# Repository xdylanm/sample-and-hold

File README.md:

# Sample and Hold

A sample and hold circuit for a modular synth (Eurorack format) based on the LF398.

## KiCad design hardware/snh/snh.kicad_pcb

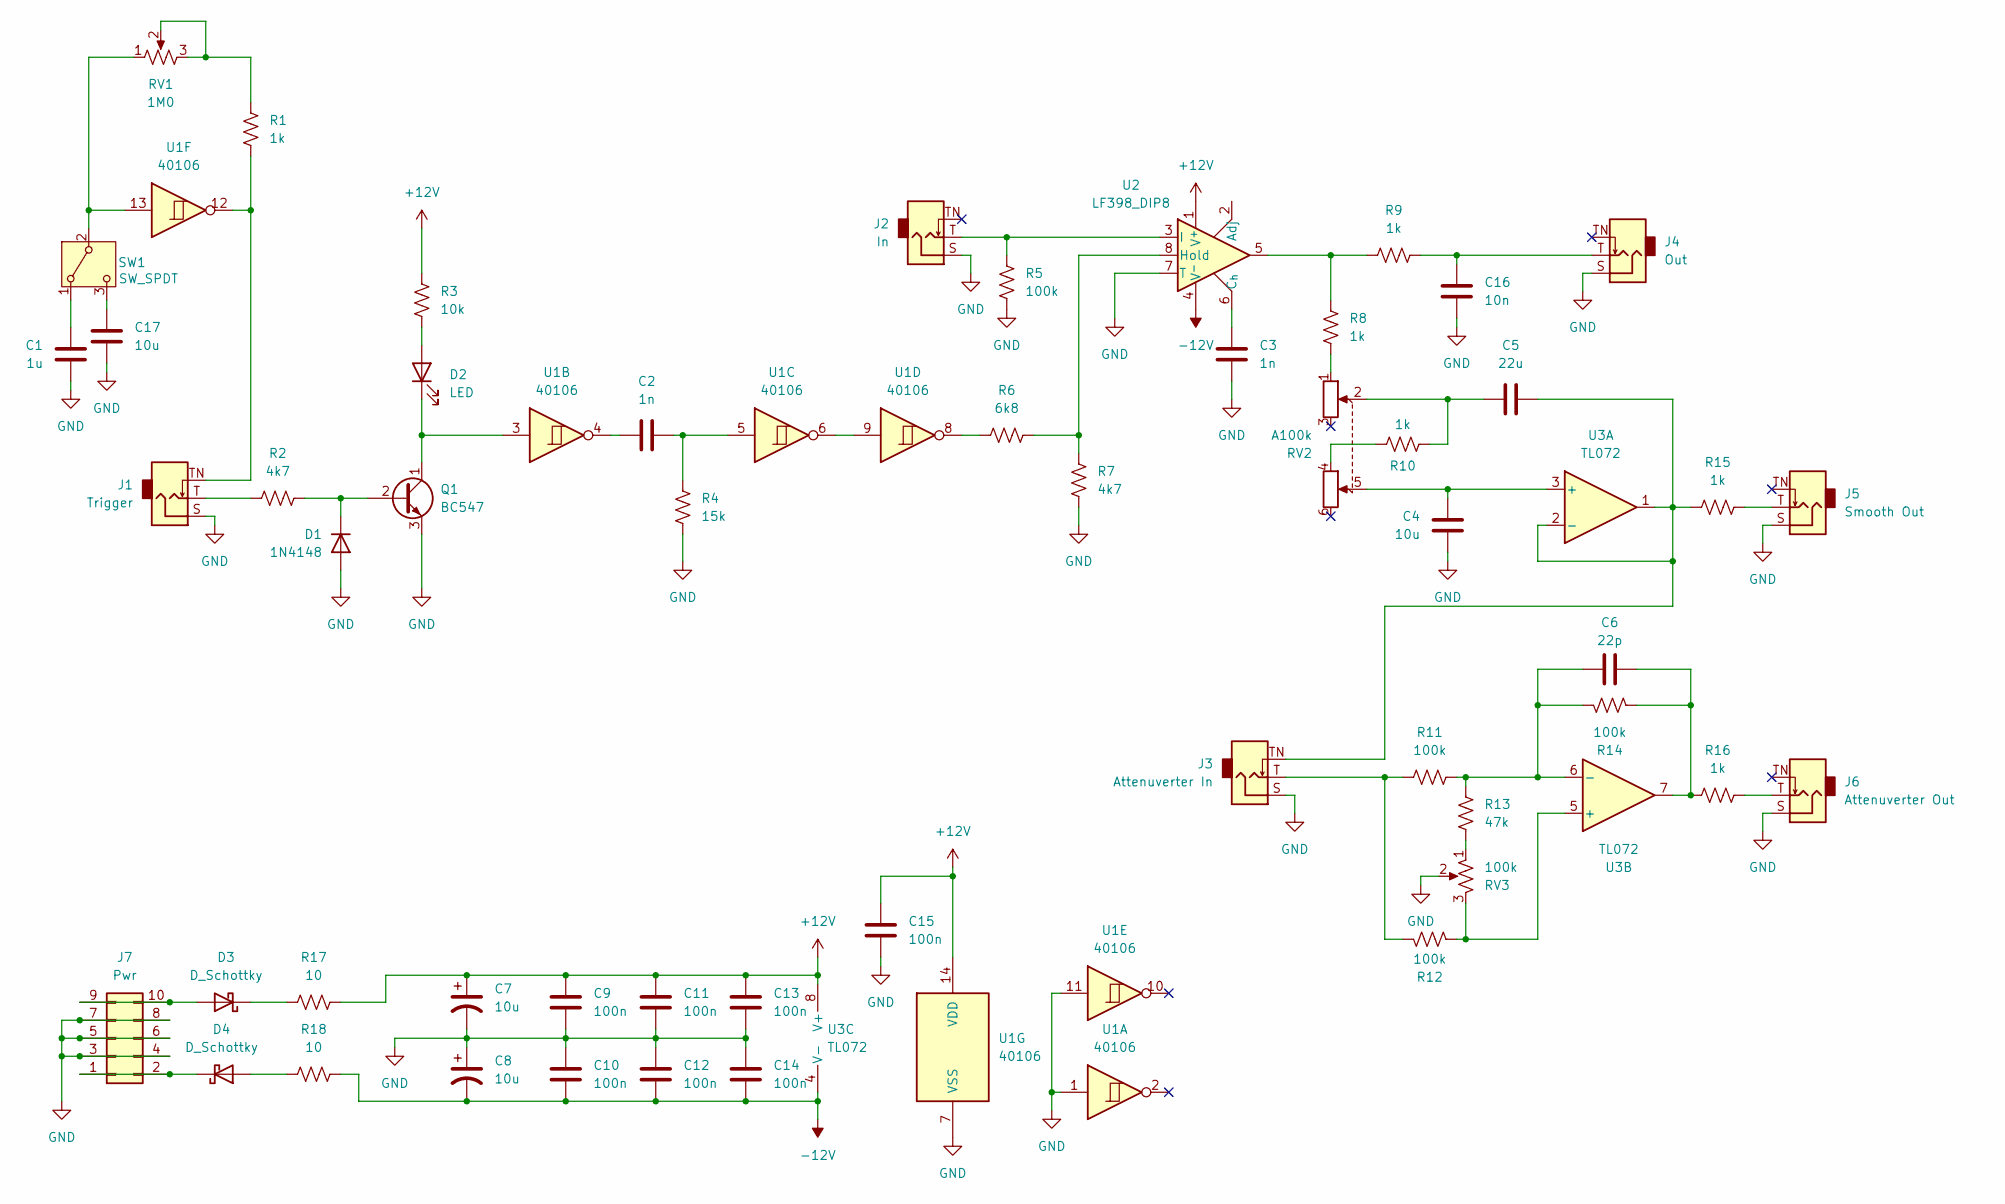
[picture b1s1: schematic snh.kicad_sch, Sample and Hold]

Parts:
C1: 1u; C_Disc_D4.7mm_W2.5mm_P5.00mm
C2: 1n; C_Disc_D5.0mm_W2.5mm_P5.00mm
C3: 1n; C_Rect_L7.0mm_W2.0mm_P5.00mm
C4, C17: 10u; C_Disc_D4.7mm_W2.5mm_P5.00mm
C5: 22u; C_Disc_D4.7mm_W2.5mm_P5.00mm
C6: 22p; C_Disc_D4.7mm_W2.5mm_P5.00mm
C7, C8: 10u; CP_Radial_D4.0mm_P2.00mm
C9, C10, C11, C12, C13, C14, C15: 100n; C_Disc_D4.7mm_W2.5mm_P5.00mm
C16: 10n; C_Disc_D4.7mm_W2.5mm_P5.00mm
D1: 1N4148; D_DO-35_SOD27_P2.54mm_Vertical_AnodeUp
D2: LED; LED_D3.0mm_Clear
D3, D4: D_Schottky; D_DO-35_SOD27_P2.54mm_Vertical_AnodeUp
J1: Trigger; Jack_3.5mm_QingPu_WQP-PJ301M-12_Vertical
J2: In; Jack_3.5mm_QingPu_WQP-PJ301M-12_Vertical
J3: Attenuverter In; Jack_3.5mm_QingPu_WQP-PJ301M-12_Vertical
J4: Out; Jack_3.5mm_QingPu_WQP-PJ301M-12_Vertical
J5: Smooth Out; Jack_3.5mm_QingPu_WQP-PJ301M-12_Vertical
J6: Attenuverter Out; Jack_3.5mm_QingPu_WQP-PJ301M-12_Vertical
J7: Pwr; IDC-Header_2x05_P2.54mm_Vertical
Q1: BC547; TO-92_Inline_Wide
R1, R8, R9, R10, R15, R16: 1k; R_Axial_DIN0204_L3.6mm_D1.6mm_P2.54mm_Vertical
R2: 4k7; R_Axial_DIN0204_L3.6mm_D1.6mm_P7.62mm_Horizontal
R3: 10k; R_Axial_DIN0204_L3.6mm_D1.6mm_P2.54mm_Vertical
R4: 15k; R_Axial_DIN0204_L3.6mm_D1.6mm_P2.54mm_Vertical
R5, R11, R12, R14: 100k; R_Axial_DIN0204_L3.6mm_D1.6mm_P2.54mm_Vertical
R6: 6k8; R_Axial_DIN0204_L3.6mm_D1.6mm_P2.54mm_Vertical
R7: 4k7; R_Axial_DIN0204_L3.6mm_D1.6mm_P2.54mm_Vertical
R13: 47k; R_Axial_DIN0204_L3.6mm_D1.6mm_P2.54mm_Vertical
R17, R18: 10; R_Axial_DIN0207_L6.3mm_D2.5mm_P10.16mm_Horizontal
RV1: 1M0; Potentiometer_Bourns_PTV09A-1_Single_Vertical
RV2: A100k; Potentiometer_Bourns_PTV112-4_Dual_Vertical
RV3: 100k; Potentiometer_Bourns_PTV09A-1_Single_Vertical
SW1: SW_SPDT; SW_Dailywell_SPDT_2MS1T1B1M1
U1: 40106; DIP-14_W7.62mm_Socket
U2: LF398_DIP8; DIP-8_W7.62mm_Socket
U3: TL072; DIP-8_W7.62mm_Socket

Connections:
+12V: C7.1, C9.1, C11.1, C13.1, C15.1, R3.1, R17.2, U1.14 (VDD), U2.1 (V^{+}), U3.8 (V+)
-12V: C8.2, C10.2, C12.2, C14.2, R18.2, U2.4 (V^{-}), U3.4 (V-)
GND: C1.1, C3.2, C4.1, C7.2, C8.1, C9.2, C10.1, C11.2, C12.1, C13.2, C14.1, C15.2, C16.2, C17.1, D1.2 (A), J1.S, J2.S, J3.S, J4.S, J5.S, J6.S, J7.3, J7.4, J7.5, J7.6, J7.7, J7.8, Q1.3 (E), R4.1, R5.1, R7.2, RV3.2, U1.1, U1.7 (VSS), U1.11, U2.7 (T)
unnamed: C2.1, U1.4
unnamed: C2.2, R4.2, U1.5
unnamed: C5.2, R10.2, RV2.2
unnamed: C6.2, R14.1, R16.2, U3.7
unnamed: C16.1, J4.T, R9.1
unnamed: D1.1 (K), Q1.2 (B), R2.1
unnamed: D2.2 (A), R3.2
unnamed: D2.1 (K), Q1.1 (C), U1.3
unnamed: D3.2 (A), J7.9, J7.10
unnamed: D3.1 (K), R17.1
unnamed: D4.2 (A), R18.1
unnamed: D4.1 (K), J7.1, J7.2
unnamed: J1.T, R2.2
unnamed: J1.TN, R1.1, U1.12
unnamed: J3.T, R11.2, R12.2
unnamed: J5.T, R15.1
unnamed: J6.T, R16.1
unnamed: R1.2, RV1.2, RV1.3
unnamed: R6.2, U1.8
unnamed: R8.1, R9.2, U2.5
unnamed: R8.2, RV2.1
unnamed: R10.1, RV2.4
unnamed: R13.2, RV3.1
unnamed: C1.2, SW1.1 (A)
unnamed: RV1.1, SW1.2 (B), U1.13
unnamed: C17.2, SW1.3 (C)
unnamed: U1.6, U1.9
unnamed: C3.1, U2.6 (C_{h})
unnamed: R6.1, R7.1, U2.8 (Hold)
unnamed: J2.T, R5.2, U2.3 (I)
unnamed: C4.2, RV2.5, U3.3 (+)
unnamed: C5.1, J3.TN, R15.2, U3.1, U3.2 (-)
unnamed: R12.1, RV3.3, U3.5 (+)
unnamed: C6.1, R11.1, R13.1, R14.2, U3.6 (-)

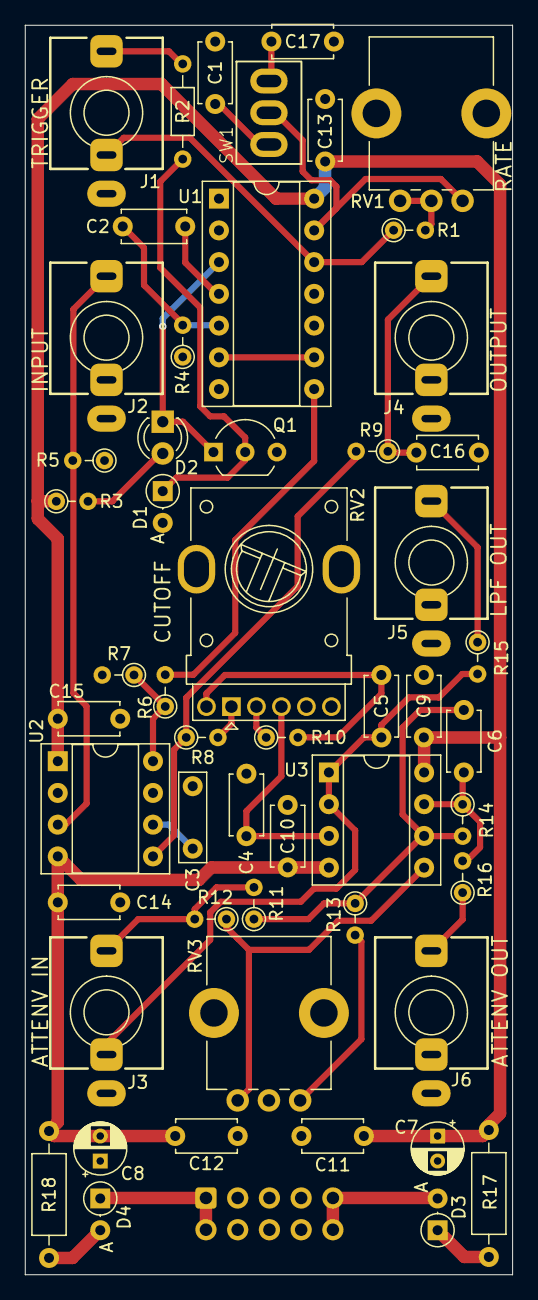
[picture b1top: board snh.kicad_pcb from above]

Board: 2 copper layers, 39.0 x 100.0 mm, 54 parts (1 on the bottom side), 37 nets.

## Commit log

2025-12-28 v1 board, no docs
2025-12-28 Updating to mkdocs+material, generated BOM and schematic (small tweaks to clean up)

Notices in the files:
hardware/snh/snh.kicad_pcb:
CC BY-SA 4.0
